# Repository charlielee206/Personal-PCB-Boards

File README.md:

# Personal-PCB-Boards
A collection of my personal PCBs and its parts. May overlap with my other projects.
Mostly made using KiCAD.

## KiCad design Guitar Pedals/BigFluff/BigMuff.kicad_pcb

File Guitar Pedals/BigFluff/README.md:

Replica of the Big Muff PI</br>
Mojo John and her Big Fluff.</br>

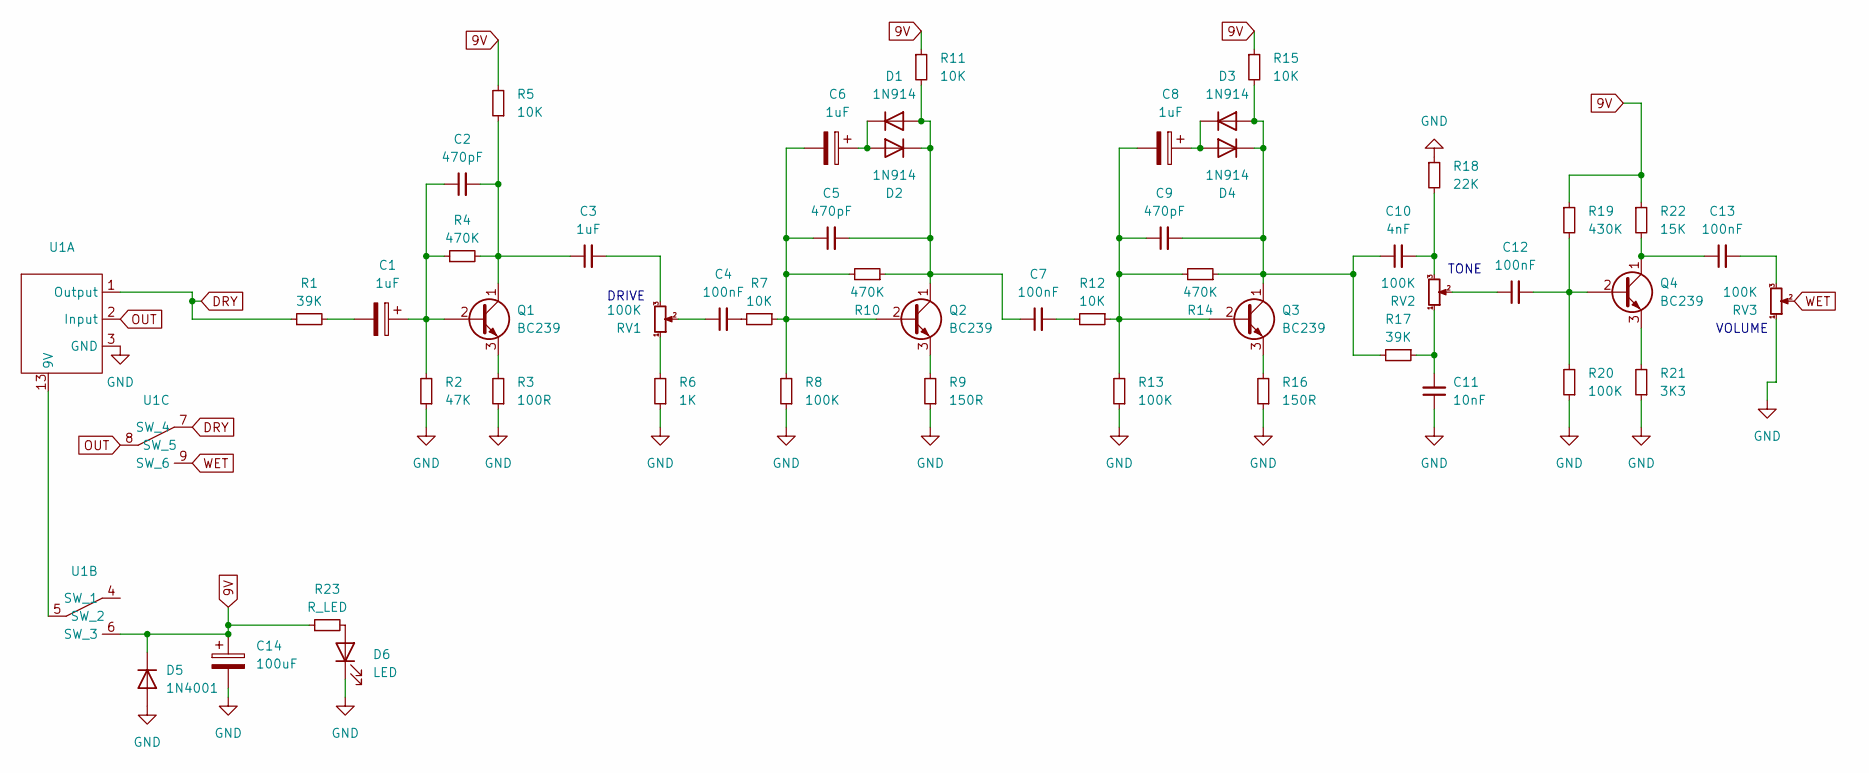
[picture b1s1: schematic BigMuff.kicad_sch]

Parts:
C1, C6, C8: 1uF; CP_Radial_D4.0mm_P2.00mm
C2, C5, C9: 470pF; C_Custom_Disc_D4.3mm_W1.9mm_P5.00mm
C3: 1uF; C_Custom_Disc_D4.3mm_W1.9mm_P5.00mm
C4, C7, C12, C13: 100nF; C_Custom_Disc_D4.3mm_W1.9mm_P5.00mm
C10: 4nF; C_Custom_Disc_D4.3mm_W1.9mm_P5.00mm
C11: 10nF; C_Custom_Disc_D4.3mm_W1.9mm_P5.00mm
C14: 100uF; CP_Radial_D6.3mm_P2.50mm
D1, D2, D3, D4: 1N914; D_DO-35_SOD27_P7.62mm_Horizontal
D5: 1N4001; D_DO-41_SOD81_P10.16mm_Horizontal
D6: LED; LED_D3.0mm
Q1, Q2, Q3, Q4: BC239; TO-92L_Inline
R1, R17: 39K; R_Custom_Axial_DIN0207_L6.3mm_D2.5mm_P7.62mm_Horizontal
R2: 47K; R_Custom_Axial_DIN0207_L6.3mm_D2.5mm_P7.62mm_Horizontal
R3: 100R; R_Custom_Axial_DIN0207_L6.3mm_D2.5mm_P7.62mm_Horizontal
R4, R10, R14: 470K; R_Custom_Axial_DIN0207_L6.3mm_D2.5mm_P7.62mm_Horizontal
R5, R7, R11, R12, R15: 10K; R_Custom_Axial_DIN0207_L6.3mm_D2.5mm_P7.62mm_Horizontal
R6: 1K; R_Custom_Axial_DIN0207_L6.3mm_D2.5mm_P7.62mm_Horizontal
R8, R13, R20: 100K; R_Custom_Axial_DIN0207_L6.3mm_D2.5mm_P7.62mm_Horizontal
R9, R16: 150R; R_Custom_Axial_DIN0207_L6.3mm_D2.5mm_P7.62mm_Horizontal
R18: 22K; R_Custom_Axial_DIN0207_L6.3mm_D2.5mm_P7.62mm_Horizontal
R19: 430K; R_Custom_Axial_DIN0207_L6.3mm_D2.5mm_P7.62mm_Horizontal
R21: 3K3; R_Custom_Axial_DIN0207_L6.3mm_D2.5mm_P7.62mm_Horizontal
R22: 15K; R_Custom_Axial_DIN0207_L6.3mm_D2.5mm_P7.62mm_Horizontal
R23: R_LED; R_Custom_Axial_DIN0207_L6.3mm_D2.5mm_P7.62mm_Horizontal
RV1, RV2, RV3: 100K; Potentiometer_Alps_RK09L_Single_Vertical
U1: EmptyPedal

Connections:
9V: C14.1, D5.1 (K), R5.2, R11.1, R15.1, R19.1, R22.1, R23.1, U1.6 (SW_3)
DRY: R1.1, U1.1 (Output), U1.7 (SW_4)
GND: C11.1, C14.2, D5.2 (A), D6.1 (K), R2.1, R3.1, R6.1, R8.1, R9.1, R13.1, R16.1, R18.1, R20.1, R21.1, RV3.1, U1.3 (GND)
unnamed: C1.2, R1.2
unnamed: C3.2, RV1.3
unnamed: C4.1, RV1.2
unnamed: C4.2, R7.2
unnamed: C7.2, R12.2
unnamed: C10.2, R18.2, RV2.3
unnamed: C11.2, R17.1, RV2.1
unnamed: C12.1, RV2.2
unnamed: C13.2, RV3.3
unnamed: C5.2, C7.1, D1.2 (A), D2.1 (K), Q2.1 (C), R10.1, R11.2
unnamed: C6.1, D1.1 (K), D2.2 (A)
unnamed: C9.2, C10.1, D3.2 (A), D4.1 (K), Q3.1 (C), R14.1, R15.2, R17.2
unnamed: C8.1, D3.1 (K), D4.2 (A)
unnamed: D6.2 (A), R23.2
unnamed: C1.1, C2.1, Q1.2 (B), R2.2, R4.1
unnamed: C2.2, C3.1, Q1.1 (C), R4.2, R5.1
unnamed: Q1.3 (E), R3.2
unnamed: C5.1, C6.2, Q2.2 (B), R7.1, R8.2, R10.2
unnamed: Q2.3 (E), R9.2
unnamed: C8.2, C9.1, Q3.2 (B), R12.1, R13.2, R14.2
unnamed: Q3.3 (E), R16.2
unnamed: C12.2, Q4.2 (B), R19.2, R20.2
unnamed: C13.1, Q4.1 (C), R22.2
unnamed: Q4.3 (E), R21.2
unnamed: R6.2, RV1.1
unnamed: U1.5 (SW_2), U1.13 (9V)
OUT: U1.2 (Input), U1.8 (SW_5)
WET: RV3.2, U1.9 (SW_6)

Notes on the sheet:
TONE
VOLUME
DRIVE

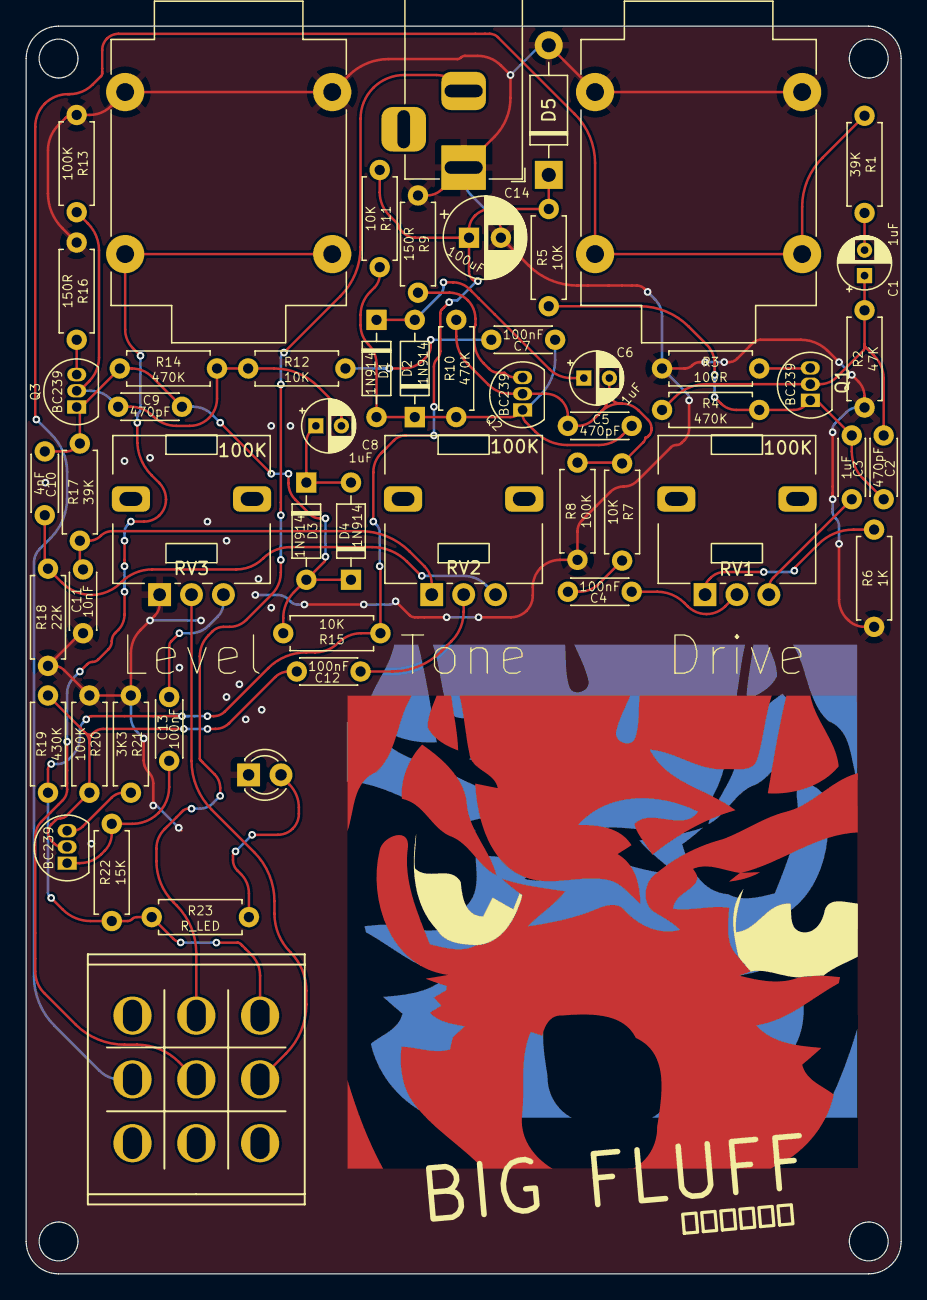
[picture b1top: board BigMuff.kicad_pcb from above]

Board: 2 copper layers, 68.6 x 97.8 mm, 51 parts (0 on the bottom side), 31 nets.

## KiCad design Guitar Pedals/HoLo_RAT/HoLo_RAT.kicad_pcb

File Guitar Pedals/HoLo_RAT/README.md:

A clone of the famous 'ProCo RAT' distortion pedal. </br>
The Transistor is wired wrong. Need to fix.</br>

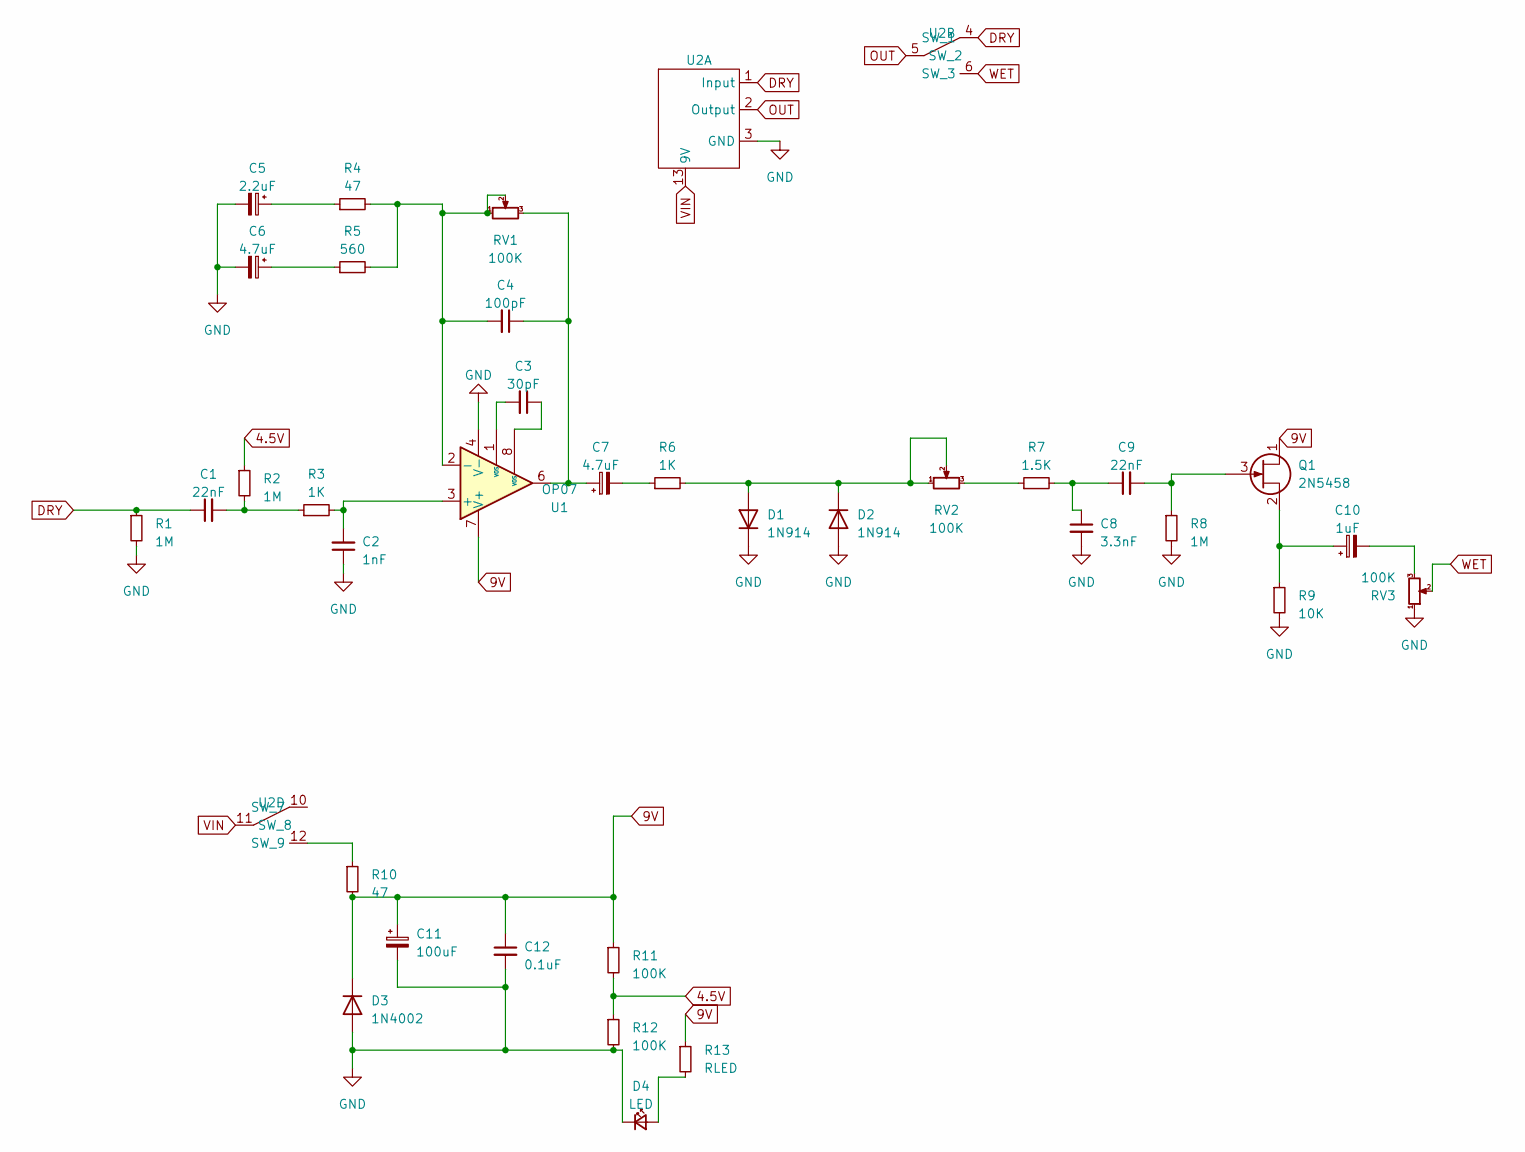
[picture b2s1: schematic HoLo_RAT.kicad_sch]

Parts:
C1, C9: 22nF; C_Custom_Disc_D4.3mm_W1.9mm_P5.00mm
C2: 1nF; C_Custom_Disc_D4.3mm_W1.9mm_P5.00mm
C3: 30pF; C_Custom_Disc_D4.3mm_W1.9mm_P5.00mm
C4: 100pF; C_Custom_Disc_D4.3mm_W1.9mm_P5.00mm
C5: 2.2uF; CP_Radial_D5.0mm_P2.00mm
C6, C7: 4.7uF; CP_Radial_D5.0mm_P2.00mm
C8: 3.3nF; C_Custom_Disc_D4.3mm_W1.9mm_P5.00mm
C10: 1uF; CP_Radial_D5.0mm_P2.00mm
C11: 100uF; CP_Radial_D5.0mm_P2.00mm
C12: 0.1uF; C_Custom_Disc_D4.3mm_W1.9mm_P5.00mm
D1, D2: 1N914; D_DO-35_SOD27_P7.62mm_Horizontal
D3: 1N4002; D_DO-41_SOD81_P10.16mm_Horizontal
D4: LED; LED_D3.0mm
Q1: 2N5458; TO-92L_Inline
R1, R2, R8: 1M; R_Custom_Axial_DIN0207_L6.3mm_D2.5mm_P7.62mm_Horizontal
R3, R6: 1K; R_Custom_Axial_DIN0207_L6.3mm_D2.5mm_P7.62mm_Horizontal
R4, R10: 47; R_Custom_Axial_DIN0207_L6.3mm_D2.5mm_P7.62mm_Horizontal
R5: 560; R_Custom_Axial_DIN0207_L6.3mm_D2.5mm_P7.62mm_Horizontal
R7: 1.5K; R_Custom_Axial_DIN0207_L6.3mm_D2.5mm_P7.62mm_Horizontal
R9: 10K; R_Custom_Axial_DIN0207_L6.3mm_D2.5mm_P7.62mm_Horizontal
R11, R12: 100K; R_Custom_Axial_DIN0207_L6.3mm_D2.5mm_P7.62mm_Horizontal
R13: RLED; R_Custom_Axial_DIN0207_L6.3mm_D2.5mm_P7.62mm_Horizontal
RV1, RV2, RV3: 100K; Potentiometer_Alps_RK09L_Single_Vertical
U1: OP07; DIP-8_W7.62mm
U2: EmptyPedal

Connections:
4.5V: R2.1, R11.2, R12.1
9V: C11.1, C12.1, D3.1 (K), Q1.1 (D), R10.2, R11.1, R13.1, U1.7 (V+)
DRY: C1.1, R1.1, U2.1 (Input), U2.4 (SW_1)
GND: C2.1, C5.2, C6.2, C8.2, C11.2, C12.2, D1.1 (K), D2.2 (A), D3.2 (A), D4.1 (K), R1.2, R8.2, R9.2, R12.2, RV3.1, U1.4 (V-), U2.3 (GND)
unnamed: C1.2, R2.2, R3.1
unnamed: C3.1, U1.8 (VOS)
unnamed: C3.2, U1.1 (VOS)
unnamed: C4.1, C7.1, RV1.3, U1.6
unnamed: C5.1, R4.1
unnamed: C6.1, R5.1
unnamed: C7.2, R6.1
unnamed: C8.1, C9.1, R7.2
unnamed: C10.2, RV3.3
unnamed: D1.2 (A), D2.1 (K), R6.2, RV2.1, RV2.2
unnamed: D4.2 (A), R13.2
unnamed: C9.2, Q1.3 (G), R8.1
unnamed: C10.1, Q1.2 (S), R9.1
unnamed: R7.1, RV2.3
unnamed: C2.2, R3.2, U1.3 (+)
unnamed: C4.2, R4.2, R5.2, RV1.1, RV1.2, U1.2 (-)
unnamed: R10.1, U2.12 (SW_9)
OUT: U2.2 (Output), U2.5 (SW_2)
VIN: U2.11 (SW_8), U2.13 (9V)
WET: RV3.2, U2.6 (SW_3)

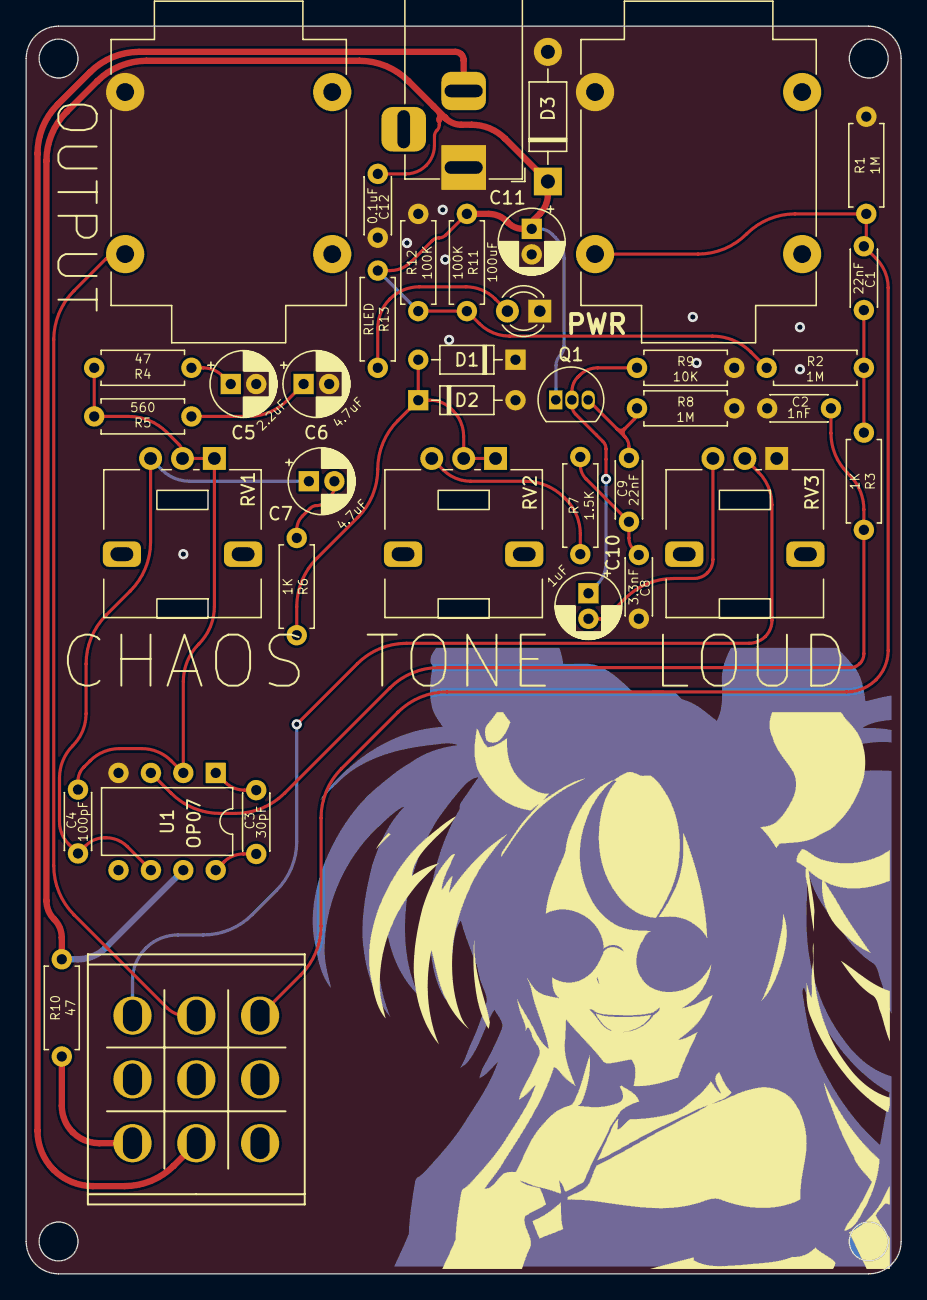
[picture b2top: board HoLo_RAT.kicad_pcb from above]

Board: 2 copper layers, 68.6 x 97.8 mm, 35 parts (0 on the bottom side), 24 nets.

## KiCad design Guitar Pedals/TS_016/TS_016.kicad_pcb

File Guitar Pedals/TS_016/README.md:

A clone of the famous 'TS808` Pedal (or TS9). This one doesn't use an actual tube though. </br>
 </br>

</br>

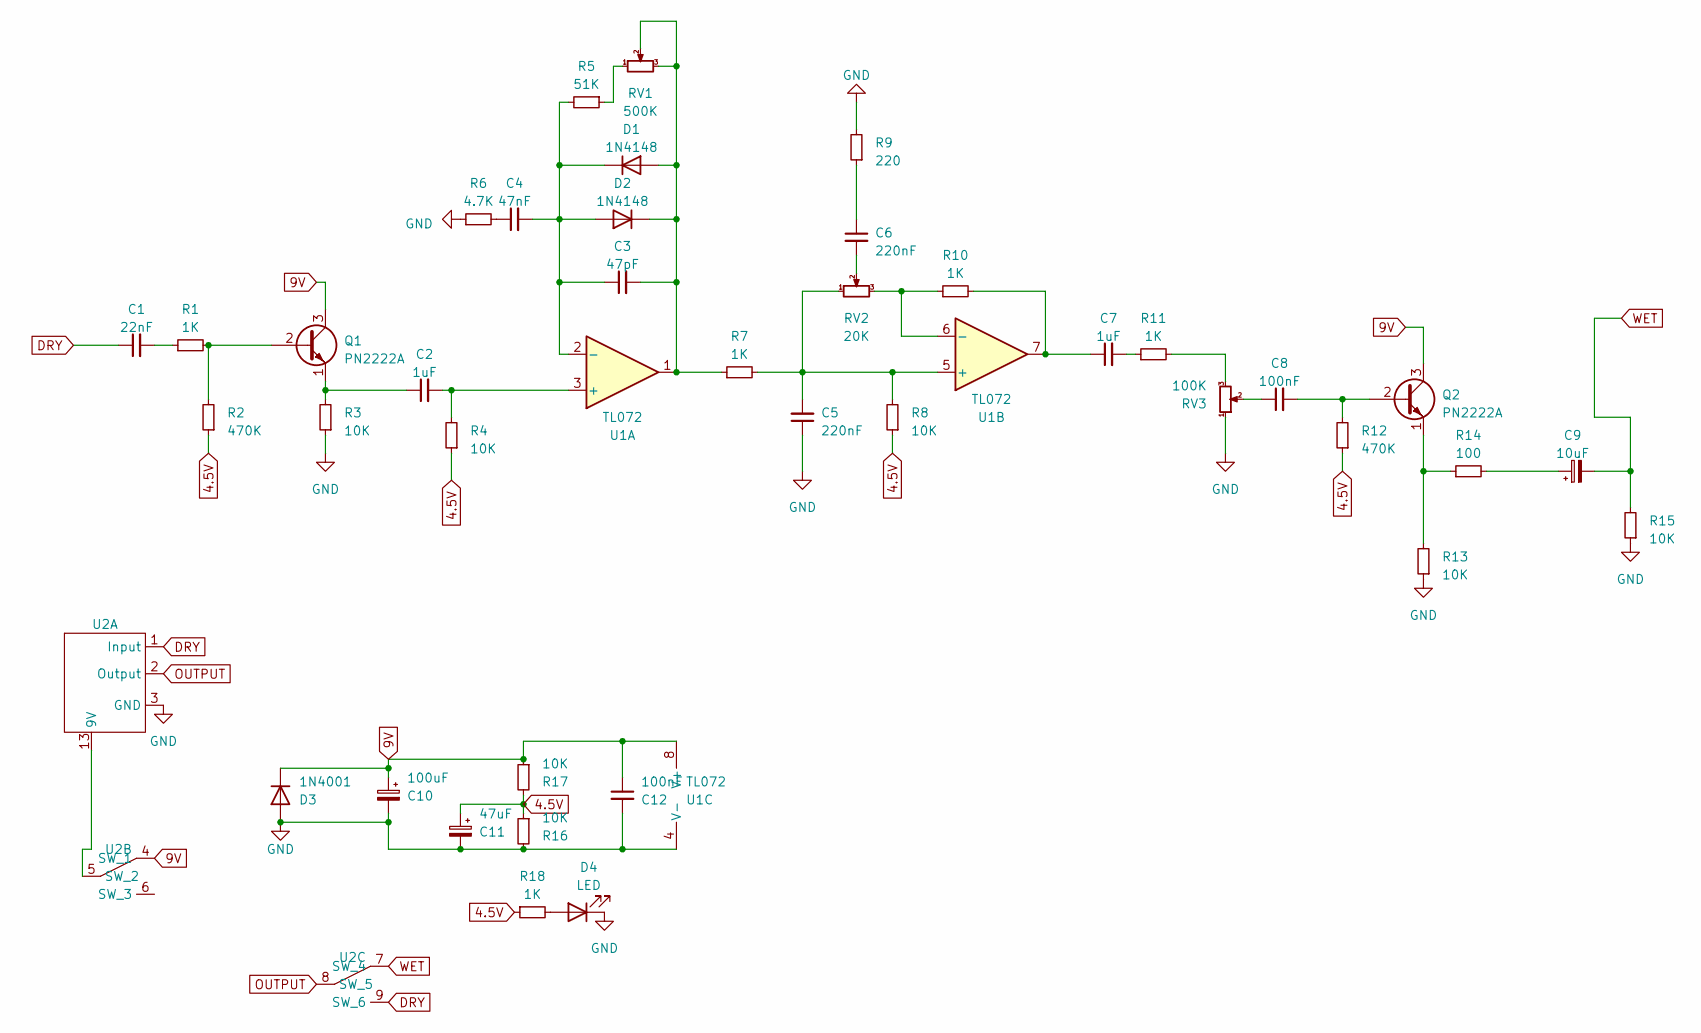
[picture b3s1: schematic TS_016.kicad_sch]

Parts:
C1: 22nF; C_Disc_D5.0mm_W2.5mm_P5.00mm
C2, C7: 1uF; C_Disc_D5.0mm_W2.5mm_P5.00mm
C3: 47pF; C_Disc_D5.0mm_W2.5mm_P5.00mm
C4: 47nF; C_Disc_D5.0mm_W2.5mm_P5.00mm
C5, C6: 220nF; C_Disc_D5.0mm_W2.5mm_P5.00mm
C8, C12: 100nF; C_Disc_D5.0mm_W2.5mm_P5.00mm
C9: 10uF; CP_Radial_D5.0mm_P2.50mm
C10: 100uF; CP_Radial_D5.0mm_P2.50mm
C11: 47uF; CP_Radial_D5.0mm_P2.50mm
D1, D2: 1N4148; D_DO-35_SOD27_P7.62mm_Horizontal
D3: 1N4001; D_DO-41_SOD81_P10.16mm_Horizontal
D4: LED; LED_D3.0mm
Q1, Q2: PN2222A; TO-92_Inline
R1, R7, R10, R11, R18: 1K; R_Axial_DIN0207_L6.3mm_D2.5mm_P7.62mm_Horizontal
R2, R12: 470K; R_Axial_DIN0207_L6.3mm_D2.5mm_P7.62mm_Horizontal
R3, R4, R8, R13, R15, R16, R17: 10K; R_Axial_DIN0207_L6.3mm_D2.5mm_P7.62mm_Horizontal
R5: 51K; R_Axial_DIN0207_L6.3mm_D2.5mm_P7.62mm_Horizontal
R6: 4.7K; R_Axial_DIN0207_L6.3mm_D2.5mm_P7.62mm_Horizontal
R9: 220; R_Axial_DIN0207_L6.3mm_D2.5mm_P7.62mm_Horizontal
R14: 100; R_Axial_DIN0207_L6.3mm_D2.5mm_P7.62mm_Horizontal
RV1: 500K; Potentiometer_Alps_RK09L_Single_Vertical
RV2: 20K; Potentiometer_Alps_RK09L_Single_Vertical
RV3: 100K; Potentiometer_Alps_RK09L_Single_Vertical
U1: TL072; DIP-8_W7.62mm
U2: EmptyPedal

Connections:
4.5V: C11.1, R2.1, R4.1, R8.1, R12.1, R16.1, R17.2, R18.1
9V: C10.1, C12.1, D3.1 (K), Q1.3 (C), Q2.3 (C), R17.1, U1.8 (V+), U2.4 (SW_1)
DRY: C1.1, U2.1 (Input), U2.9 (SW_6)
GND: C5.1, C10.2, C11.2, C12.2, D3.2 (A), D4.1 (K), R3.1, R6.1, R9.2, R13.1, R15.1, R16.2, RV3.1, U1.4 (V-), U2.3 (GND)
unnamed: C1.2, R1.1
unnamed: C4.1, R6.2
unnamed: C6.1, R9.1
unnamed: C6.2, RV2.2
unnamed: C7.1, R10.2, U1.7
unnamed: C7.2, R11.1
unnamed: C8.1, RV3.2
unnamed: C9.1, R14.2
unnamed: C3.2, D1.2 (A), D2.1 (K), R7.1, RV1.2, RV1.3, U1.1
unnamed: C3.1, C4.2, D1.1 (K), D2.2 (A), R5.2, U1.2 (-)
unnamed: D4.2 (A), R18.2
unnamed: Q1.2 (B), R1.2, R2.2
unnamed: C2.1, Q1.1 (E), R3.2
unnamed: C8.2, Q2.2 (B), R12.2
unnamed: Q2.1 (E), R13.2, R14.1
unnamed: R5.1, RV1.1
unnamed: R11.2, RV3.3
unnamed: C2.2, R4.2, U1.3 (+)
unnamed: C5.2, R7.2, R8.2, RV2.1, U1.5 (+)
unnamed: R10.1, RV2.3, U1.6 (-)
unnamed: U2.5 (SW_2), U2.13 (9V)
OUTPUT: U2.2 (Output), U2.8 (SW_5)
WET: C9.2, R15.2, U2.7 (SW_4)

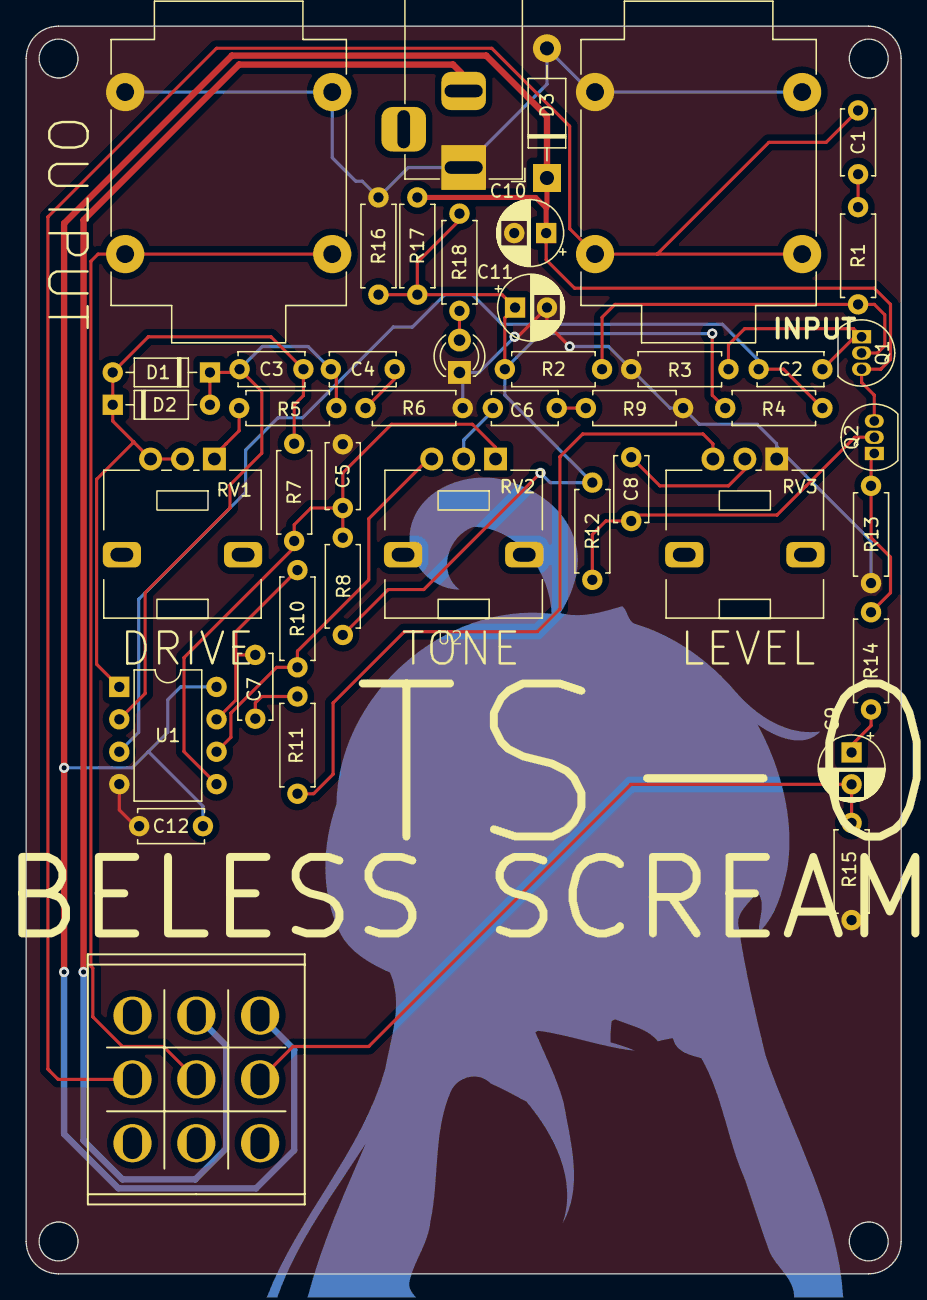
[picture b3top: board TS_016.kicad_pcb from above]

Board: 2 copper layers, 68.6 x 97.8 mm, 41 parts (0 on the bottom side), 27 nets.

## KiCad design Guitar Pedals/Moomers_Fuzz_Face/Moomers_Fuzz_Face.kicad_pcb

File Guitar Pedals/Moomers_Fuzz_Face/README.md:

A clone of the 'Fuzz Face' (or tone bender or arbiter fuzz or whatever).</br>

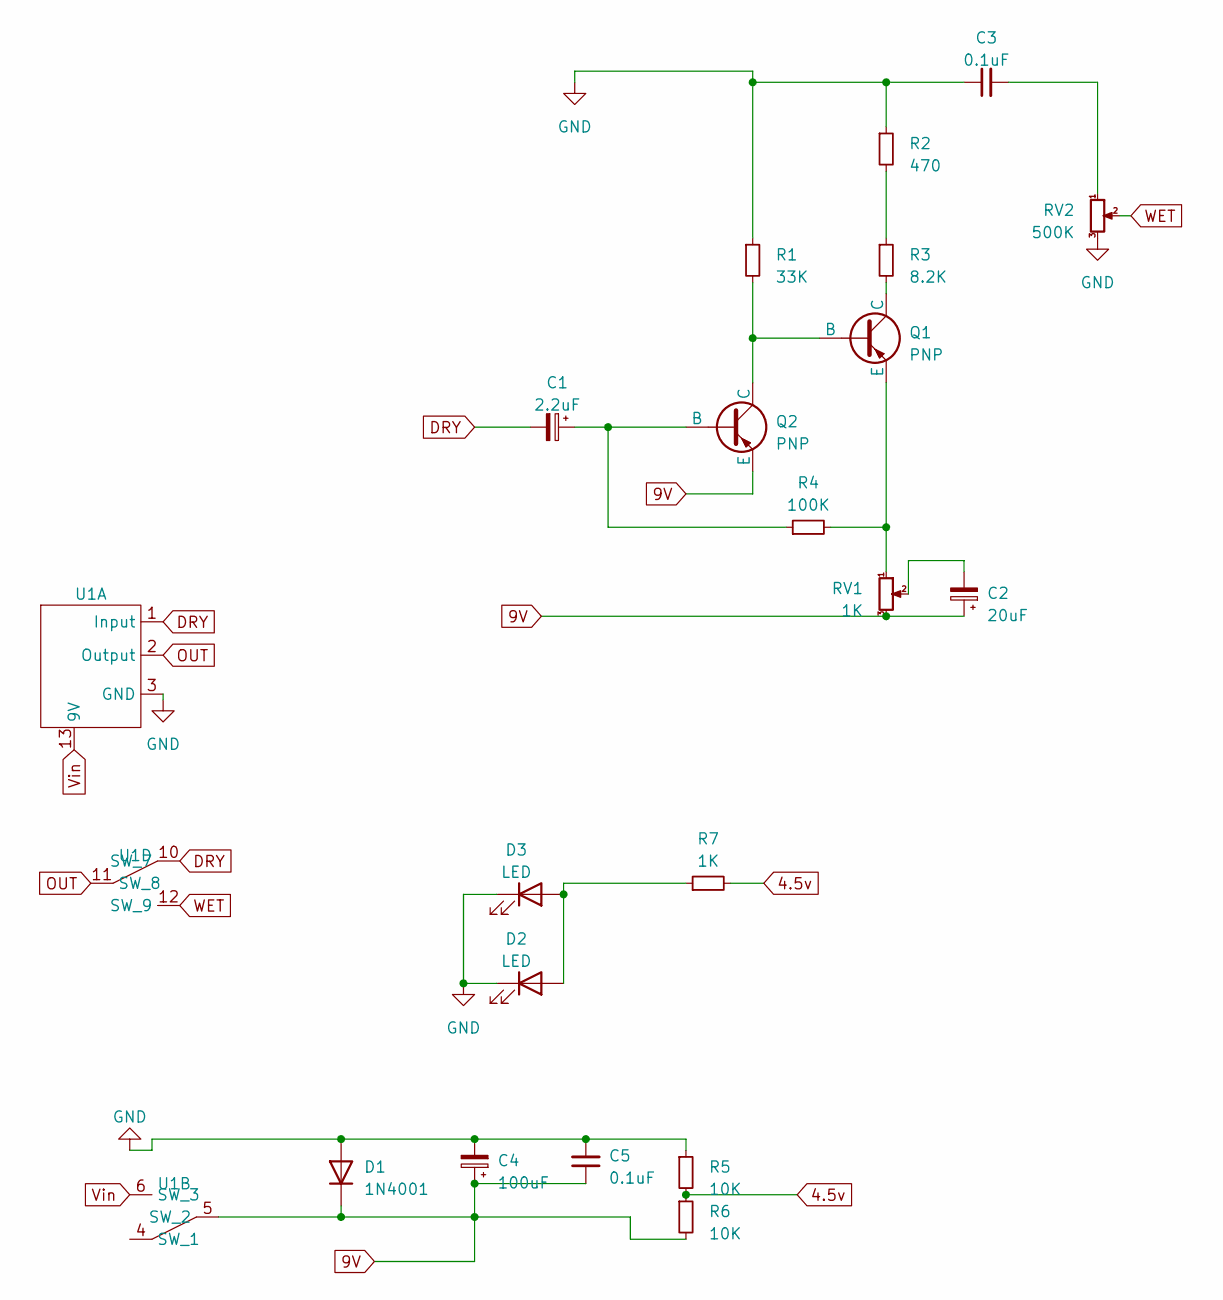
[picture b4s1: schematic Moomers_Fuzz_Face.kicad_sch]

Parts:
C1: 2.2uF; CP_Radial_Tantal_D6.0mm_P2.50mm
C2: 20uF; CP_Radial_Tantal_D6.0mm_P2.50mm
C3, C5: 0.1uF; C_Disc_D4.7mm_W2.5mm_P5.00mm
C4: 100uF; CP_Radial_Tantal_D6.0mm_P2.50mm
D1: 1N4001; D_DO-41_SOD81_P10.16mm_Horizontal
D2, D3: LED; PinHeader_1x02_P2.54mm_Vertical
Q1, Q2: PNP; TO-39-3
R1: 33K; R_Axial_DIN0207_L6.3mm_D2.5mm_P7.62mm_Horizontal
R2: 470; R_Axial_DIN0207_L6.3mm_D2.5mm_P7.62mm_Horizontal
R3: 8.2K; R_Axial_DIN0207_L6.3mm_D2.5mm_P7.62mm_Horizontal
R4: 100K; R_Axial_DIN0207_L6.3mm_D2.5mm_P7.62mm_Horizontal
R5, R6: 10K; R_Axial_DIN0207_L6.3mm_D2.5mm_P7.62mm_Horizontal
R7: 1K; R_Axial_DIN0207_L6.3mm_D2.5mm_P7.62mm_Horizontal
RV1: 1K; Potentiometer_Alps_RK09L_Single_Vertical
RV2: 500K; Potentiometer_Alps_RK09L_Single_Vertical
U1: EmptyPedal

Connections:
4.5v: R5.2, R6.1, R7.2
9V: C2.1, C4.1, C5.1, D1.1 (K), Q2.3 (E), R6.2, RV1.3, U1.5 (SW_2)
DRY: C1.2, U1.1 (Input), U1.10 (SW_7)
GND: C3.1, C4.2, C5.2, D1.2 (A), D2.1 (K), D3.1 (K), R1.1, R2.1, R5.1, RV2.3, U1.3 (GND)
unnamed: C2.2, RV1.2
unnamed: C3.2, RV2.1
unnamed: D2.2 (A), D3.2 (A), R7.1
unnamed: Q1.2 (B), Q2.1 (C), R1.2
unnamed: Q1.1 (C), R3.2
unnamed: Q1.3 (E), R4.2, RV1.1
unnamed: C1.1, Q2.2 (B), R4.1
unnamed: R2.2, R3.1
OUT: U1.2 (Output), U1.11 (SW_8)
Vin: U1.6 (SW_3), U1.13 (9V)
WET: RV2.2, U1.12 (SW_9)

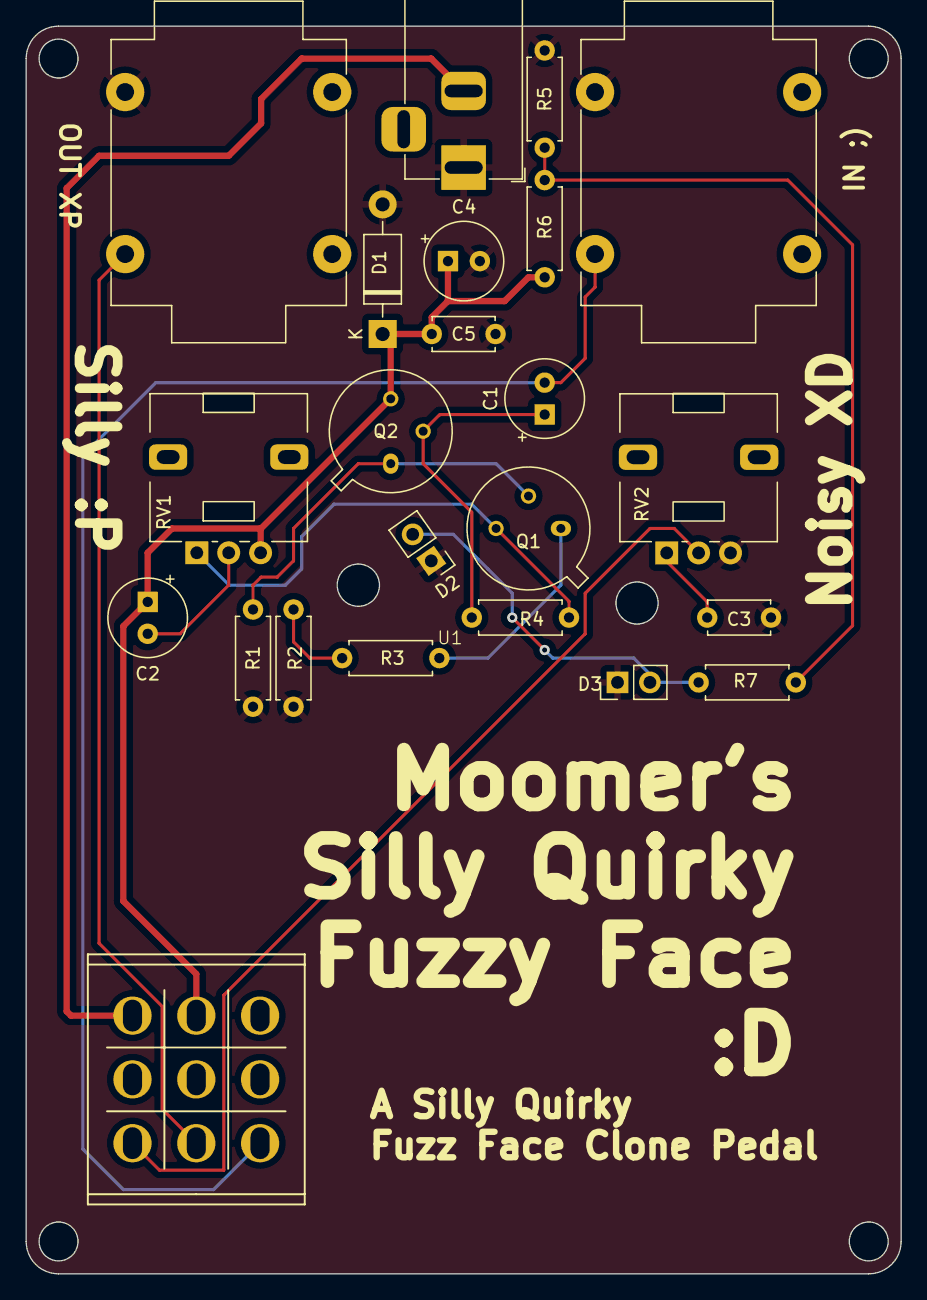
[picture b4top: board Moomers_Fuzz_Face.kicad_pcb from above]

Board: 2 copper layers, 68.6 x 97.8 mm, 20 parts (0 on the bottom side), 15 nets.

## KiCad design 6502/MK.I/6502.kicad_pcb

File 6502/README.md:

My adventures with the Ben Eater 6502 computer.

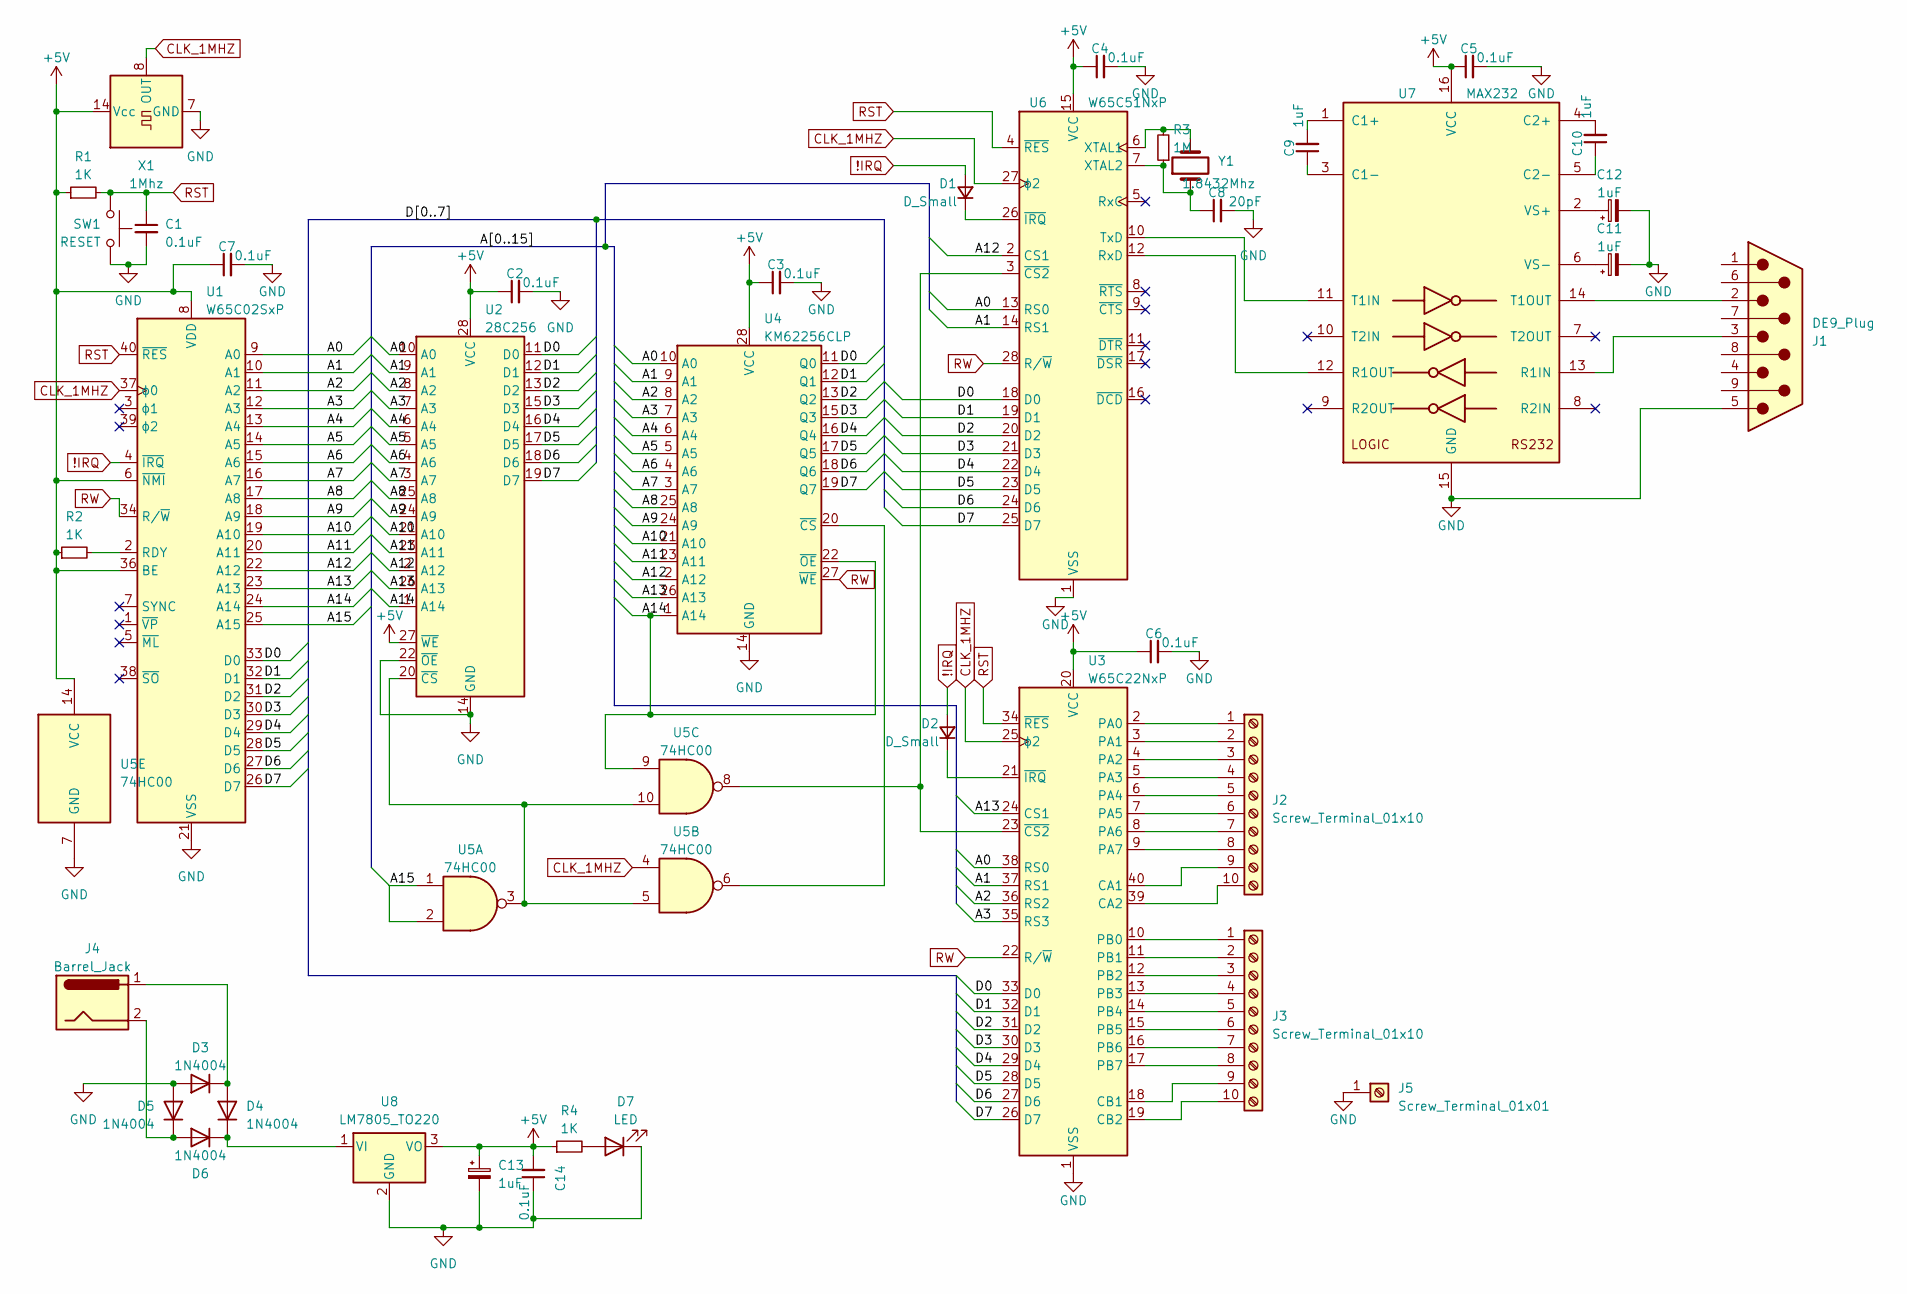
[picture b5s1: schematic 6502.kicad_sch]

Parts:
C1, C2, C3, C4, C5, C6, C7, C14: 0.1uF; C_Disc_D4.3mm_W1.9mm_P5.00mm
C8: 20pF; C_Disc_D4.3mm_W1.9mm_P5.00mm
C9, C10, C11, C12, C13: 1uF; CP_Radial_D6.3mm_P2.50mm
D1, D2: D_Small; D_DO-35_SOD27_P7.62mm_Horizontal
D3, D4, D5, D6: 1N4004; D_DO-41_SOD81_P10.16mm_Horizontal
D7: LED; LED_D5.0mm
J1: DE9_Plug; DSUB-9_Female_Horizontal_P2.77x2.84mm_EdgePinOffset4.94mm_H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
J2, J3: Screw_Terminal_01x10; PinHeader_1x10_P2.54mm_Vertical
J4: Barrel_Jack; BarrelJack_Horizontal
J5: Screw_Terminal_01x01; PinHeader_1x01_P2.54mm_Vertical
R1, R2, R4: 1K; R_Axial_DIN0207_L6.3mm_D2.5mm_P7.62mm_Horizontal
R3: 1M; R_Axial_DIN0207_L6.3mm_D2.5mm_P7.62mm_Horizontal
SW1: RESET; SW_PUSH_6mm
U1: W65C02SxP; DIP-40_W15.24mm
U2: 28C256; DIP-28_W15.24mm
U3: W65C22NxP; DIP-40_W15.24mm
U4: KM62256CLP; DIP-28_W15.24mm
U5: 74HC00; DIP-14_W7.62mm
U6: W65C51NxP; DIP-28_W15.24mm
U7: MAX232; DIP-16_W7.62mm
U8: LM7805_TO220; TO-220-3_Vertical
X1: 1Mhz; Oscillator_DIP-14
Y1: 1.8432Mhz; Crystal_HC18-U_Vertical

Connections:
!IRQ: D1.2 (A), D2.2 (A), U1.4 (~IRQ)
+5V: C2.1, C3.1, C4.1, C5.1, C6.1, C7.1, C13.1, C14.2, R1.1, R2.1, R4.1, U1.6 (~NMI), U1.8 (VDD), U1.36 (BE), U2.27 (~WE), U2.28 (VCC), U3.20 (VCC), U4.28 (VCC), U5.14 (VCC), U6.15 (VCC), U7.16 (VCC), U8.3 (VO), X1.14 (Vcc)
/A0: U1.9 (A0), U2.10 (A0), U3.38 (RS0), U4.10 (A0), U6.13 (RS0)
/A1: U1.10 (A1), U2.9 (A1), U3.37 (RS1), U4.9 (A1), U6.14 (RS1)
/A2: U1.11 (A2), U2.8 (A2), U3.36 (RS2), U4.8 (A2)
/A3: U1.12 (A3), U2.7 (A3), U3.35 (RS3), U4.7 (A3)
/A4: U1.13 (A4), U2.6 (A4), U4.6 (A4)
/A5: U1.14 (A5), U2.5 (A5), U4.5 (A5)
/A6: U1.15 (A6), U2.4 (A6), U4.4 (A6)
/A7: U1.16 (A7), U2.3 (A7), U4.3 (A7)
/A8: U1.17 (A8), U2.25 (A8), U4.25 (A8)
/A9: U1.18 (A9), U2.24 (A9), U4.24 (A9)
/A10: U1.19 (A10), U2.21 (A10), U4.21 (A10)
/A11: U1.20 (A11), U2.23 (A11), U4.23 (A11)
/A12: U1.22 (A12), U2.2 (A12), U4.2 (A12), U6.2 (CS1)
/A13: U1.23 (A13), U2.26 (A13), U3.24 (CS1), U4.26 (A13)
/A14: U1.24 (A14), U2.1 (A14), U4.1 (A14), U4.22 (~OE), U5.9
/A15: U1.25 (A15), U5.1, U5.2
/D0: U1.33 (D0), U2.11 (D0), U3.33 (D0), U4.11 (Q0), U6.18 (D0)
/D1: U1.32 (D1), U2.12 (D1), U3.32 (D1), U4.12 (Q1), U6.19 (D1)
/D2: U1.31 (D2), U2.13 (D2), U3.31 (D2), U4.13 (Q2), U6.20 (D2)
/D3: U1.30 (D3), U2.15 (D3), U3.30 (D3), U4.15 (Q3), U6.21 (D3)
/D4: U1.29 (D4), U2.16 (D4), U3.29 (D4), U4.16 (Q4), U6.22 (D4)
/D5: U1.28 (D5), U2.17 (D5), U3.28 (D5), U4.17 (Q5), U6.23 (D5)
/D6: U1.27 (D6), U2.18 (D6), U3.27 (D6), U4.18 (Q6), U6.24 (D6)
/D7: U1.26 (D7), U2.19 (D7), U3.26 (D7), U4.19 (Q7), U6.25 (D7)
CLK_1MHZ: U1.37 (ϕ0), U3.25 (ϕ2), U5.4, U6.27 (ϕ2), X1.8 (OUT)
GND: C1.2, C2.2, C3.2, C4.2, C5.2, C6.2, C7.2, C8.2, C11.2, C12.2, C13.2, C14.1, D3.2 (A), D5.2 (A), D7.1 (K), J1.5, J5.1, SW1.1, U1.21 (VSS), U2.14 (GND), U2.22 (~OE), U3.1 (VSS), U4.14 (GND), U5.7 (GND), U6.1 (VSS), U7.15 (GND), U8.2 (GND), X1.7 (GND); also elsewhere on the board
unnamed: D1.1 (K), U6.26 (~IRQ)
unnamed: D2.1 (K), U3.21 (~IRQ)
unnamed: D3.1 (K), D4.2 (A), J4.1
unnamed: D4.1 (K), D6.1 (K), U8.1 (VI)
unnamed: D5.1 (K), D6.2 (A), J4.2
unnamed: D7.2 (A), R4.2
unnamed: J2.1, U3.2 (PA0)
unnamed: J2.2, U3.3 (PA1)
unnamed: J2.3, U3.4 (PA2)
unnamed: J2.4, U3.5 (PA3)
unnamed: J2.5, U3.6 (PA4)
unnamed: J2.6, U3.7 (PA5)
unnamed: J2.7, U3.8 (PA6)
unnamed: J2.8, U3.9 (PA7)
unnamed: J2.9, U3.40 (CA1)
unnamed: J2.10, U3.39 (CA2)
unnamed: J3.1, U3.10 (PB0)
unnamed: J3.2, U3.11 (PB1)
unnamed: J3.3, U3.12 (PB2)
unnamed: J3.4, U3.13 (PB3)
unnamed: J3.5, U3.14 (PB4)
unnamed: J3.6, U3.15 (PB5)
unnamed: J3.7, U3.16 (PB6)
unnamed: J3.8, U3.17 (PB7)
unnamed: J3.9, U3.18 (CB1)
unnamed: J3.10, U3.19 (CB2)
unnamed: R2.2, U1.2 (RDY)
unnamed: U2.20 (~CS), U5.3, U5.5, U5.10
unnamed: U3.23 (~CS2), U5.8, U6.3 (~CS2)
unnamed: U4.20 (~CS), U5.6
unnamed: U6.12 (RxD), U7.12 (R1OUT)
unnamed: U6.10 (TxD), U7.11 (T1IN)
unnamed: R3.2, U6.6 (XTAL1), Y1.2
unnamed: C8.1, R3.1, U6.7 (XTAL2), Y1.1
unnamed: C9.2, U7.1 (C1+)
unnamed: C9.1, U7.3 (C1-)
unnamed: C10.2, U7.4 (C2+)
unnamed: C10.1, U7.5 (C2-)
unnamed: J1.3, U7.13 (R1IN)
unnamed: J1.2, U7.14 (T1OUT)
unnamed: C12.1, U7.2 (VS+)
unnamed: C11.1, U7.6 (VS-)
RST: C1.1, R1.2, SW1.2, U1.40 (~RES), U3.34 (~RES), U6.4 (~RES)
RW: U1.34 (R/~W), U3.22 (R/~W), U4.27 (~WE), U6.28 (R/~W)
